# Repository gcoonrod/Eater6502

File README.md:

<!--
 Copyright 2023 Greg Coonrod
 
 Licensed under the Apache License, Version 2.0 (the "License");
 you may not use this file except in compliance with the License.
 You may obtain a copy of the License at
 
     http://www.apache.org/licenses/LICENSE-2.0
 
 Unless required by applicable law or agreed to in writing, software
 distributed under the License is distributed on an "AS IS" BASIS,
 WITHOUT WARRANTIES OR CONDITIONS OF ANY KIND, either express or implied.
 See the License for the specific language governing permissions and
 limitations under the License.
-->

# Eater 6502 - Computer Build

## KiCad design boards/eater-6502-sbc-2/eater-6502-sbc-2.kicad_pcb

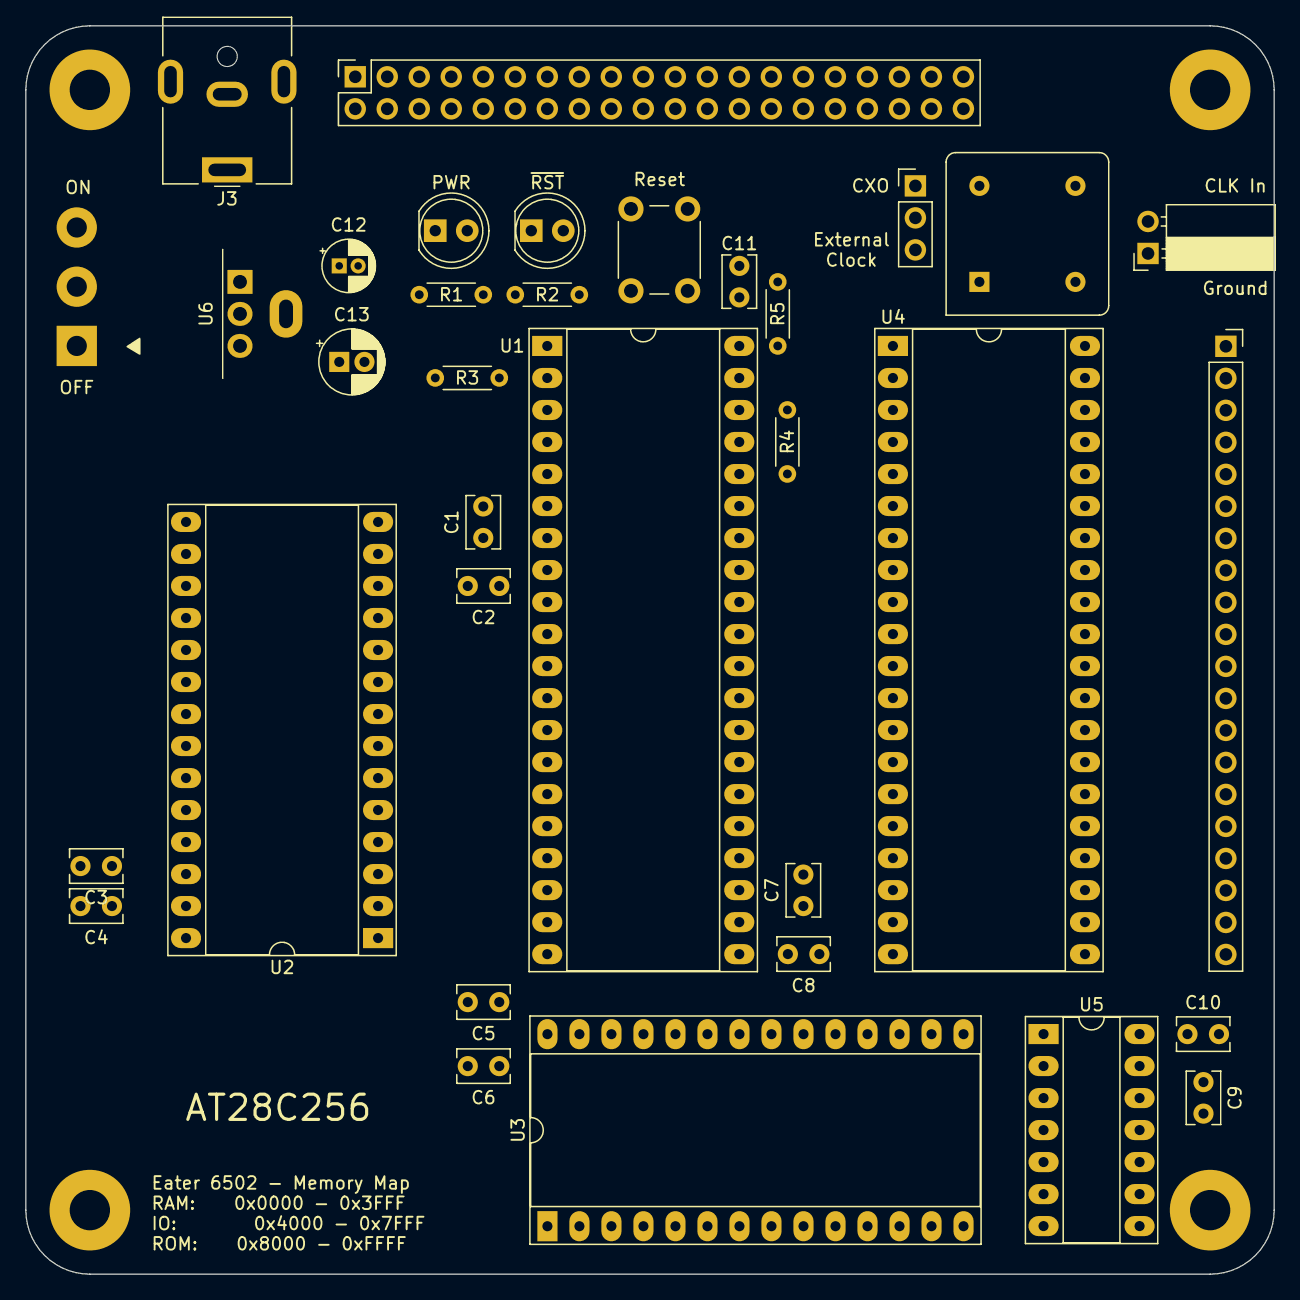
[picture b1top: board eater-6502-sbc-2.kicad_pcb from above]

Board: 2 copper layers, 99.1 x 99.1 mm, 39 parts (0 on the bottom side), 70 nets, no tracks yet.

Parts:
C1, C3, C5, C7, C9: 1u; C_Rect_L4.0mm_W2.5mm_P2.50mm
C2, C4, C6, C8, C10, C11: 100n; C_Rect_L4.0mm_W2.5mm_P2.50mm
C12: 0u33; CP_Radial_D4.0mm_P1.50mm
C13: 10u; CP_Radial_D5.0mm_P2.00mm
D1: LED_PWR; LED_D5.0mm
D2: LED_RST; LED_D5.0mm
H1, H2, H3, H4: M3; MountingHole_3.2mm_M3_Pad
HS1: Heatsink; Heatsink_AAVID_576802B03900G
J1: HDR_EXT_CLK; PinSocket_1x02_P2.54mm_Horizontal
J2: HDR_CPU_BUS; PinSocket_2x20_P2.54mm_Vertical
J3: Jack-DC; BarrelJack_CUI_PJ-063AH_Horizontal
J4: HDR_PIO_PORT; PinSocket_1x20_P2.54mm_Vertical
JP1: JMP_CLK; PinHeader_1x03_P2.54mm_Vertical
R1, R2: 470; R_Axial_DIN0204_L3.6mm_D1.6mm_P5.08mm_Horizontal
R3, R4, R5: 1k; R_Axial_DIN0204_L3.6mm_D1.6mm_P5.08mm_Horizontal
SW1: SW_RESET; SW_PUSH_6mm
SW2: SW_PWR; Button_Switch_SPST_NKK_CS12ANW03
U1: W65C02SxP; DIP-40_W15.24mm_Socket_LongPads
U2: 28C256; DIP-28_W15.24mm_Socket_LongPads
U3: KM62256CLP; DIP-28_W15.24mm_Socket_LongPads
U4: W65C22NxP; DIP-40_W15.24mm_Socket_LongPads
U5: 74HC132; DIP-14_W7.62mm_Socket_LongPads
U6: MC7805; TO-220-3_Vertical
X1: 14 MHz; Oscillator_DIP-8

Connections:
/A0: J2.17, U1.9 (A0), U2.10 (A0), U3.10 (A0), U4.38 (RS0)
/A1: J2.19, U1.10 (A1), U2.9 (A1), U3.9 (A1), U4.37 (RS1)
/A2: J2.21, U1.11 (A2), U2.8 (A2), U3.8 (A2), U4.36 (RS2)
/A3: J2.23, U1.12 (A3), U2.7 (A3), U3.7 (A3), U4.35 (RS3)
/A4: J2.25, U1.13 (A4), U2.6 (A4), U3.6 (A4)
/A5: J2.27, U1.14 (A5), U2.5 (A5), U3.5 (A5)
/A6: J2.29, U1.15 (A6), U2.4 (A6), U3.4 (A6)
/A7: J2.31, U1.16 (A7), U2.3 (A7), U3.3 (A7)
/A8: J2.33, U1.17 (A8), U2.25 (A8), U3.25 (A8)
/A9: J2.35, U1.18 (A9), U2.24 (A9), U3.24 (A9)
/A10: J2.37, U1.19 (A10), U2.21 (A10), U3.21 (A10)
/A11: J2.39, U1.20 (A11), U2.23 (A11), U3.23 (A11)
/A12: J2.38, U1.22 (A12), U2.2 (A12), U3.2 (A12)
/A13: J2.36, U1.23 (A13), U2.26 (A13), U3.26 (A13), U4.24 (CS1)
/A14: J2.34, U1.24 (A14), U2.1 (A14), U3.1 (A14), U3.22 (~OE), U5.5
/A15: J2.32, U1.25 (A15), U5.1, U5.2
/ADDR_~HI: U2.20 (~CS), U5.3, U5.4, U5.9
/BE: J2.10, R4.1, U1.36 (BE)
/CA1: J4.9, U4.40 (CA1)
/CA2: J4.10, U4.39 (CA2)
/CB1: J4.11, U4.18 (CB1)
/CB2: J4.12, U4.19 (CB2)
/CLK: J2.8, JP1.2 (C), U1.37 (ϕ0), U4.25 (ϕ2), U5.10
/CLK2: J2.4, U1.39 (ϕ2)
/CXO: JP1.1 (A), X1.5 (OUT)
/D0: J2.16, U1.33 (D0), U2.11 (D0), U3.11 (Q0), U4.33 (D0)
/D1: J2.18, U1.32 (D1), U2.12 (D1), U3.12 (Q1), U4.32 (D1)
/D2: J2.20, U1.31 (D2), U2.13 (D2), U3.13 (Q2), U4.31 (D2)
/D3: J2.22, U1.30 (D3), U2.15 (D3), U3.15 (Q3), U4.30 (D3)
/D4: J2.24, U1.29 (D4), U2.16 (D4), U3.16 (Q4), U4.29 (D4)
/D5: J2.26, U1.28 (D5), U2.17 (D5), U3.17 (Q5), U4.28 (D5)
/D6: J2.28, U1.27 (D6), U2.18 (D6), U3.18 (Q6), U4.27 (D6)
/D7: J2.30, U1.26 (D7), U2.19 (D7), U3.19 (Q7), U4.26 (D7)
/EXT_CLK: J1.2, JP1.3 (B)
/PA0: J4.1, U4.2 (PA0)
/PA1: J4.2, U4.3 (PA1)
/PA2: J4.3, U4.4 (PA2)
/PA3: J4.4, U4.5 (PA3)
/PA4: J4.5, U4.6 (PA4)
/PA5: J4.6, U4.7 (PA5)
/PA6: J4.7, U4.8 (PA6)
/PA7: J4.8, U4.9 (PA7)
/PB0: J4.13, U4.10 (PB0)
/PB1: J4.14, U4.11 (PB1)
/PB2: J4.15, U4.12 (PB2)
/PB3: J4.16, U4.13 (PB3)
/PB4: J4.17, U4.14 (PB4)
/PB5: J4.18, U4.15 (PB5)
/PB6: J4.19, U4.16 (PB6)
/PB7: J4.20, U4.17 (PB7)
/RAM_~EN: U3.20 (~CS), U5.8
/RDY: J2.3, R3.2, U1.2 (RDY)
/R/~W: J2.14, U1.34 (R/~W), U3.27 (~WE), U4.22 (R/~W)
/SYNC: J2.13, U1.7 (SYNC)
/VIA_~CS2: U4.23 (~CS2), U5.6
/~CLK: J2.5, U1.3 (ϕ1)
/~IRQ: J2.7, U1.4 (~IRQ), U4.21 (~IRQ)
/~ML: J2.9, U1.5 (~ML)
/~NMI: J2.11, U1.6 (~NMI)
/~RES: J2.2, U1.40 (~RES), U4.34 (~RES), U5.12, U5.13
/~RST: C11.2, R5.2, SW1.2
/~SO: J2.6, U1.38 (~SO)
/~VP: J2.1, U1.1 (~VP)
GND: C1.2, C2.2, C3.2, C4.2, C5.2, C6.2, C7.2, C8.2, C9.2, C10.2, C11.1, C12.2, C13.2, H1.1, H2.1, H3.1, H4.1, J1.1, J2.40, J3.2, R1.2, R2.2, SW1.1, U1.21 (VSS), U2.14 (GND), U2.22 (~OE), U3.14 (GND), U4.1 (VSS), U5.7 (GND), U6.2 (GND), X1.4 (GND)
unnamed: D1.1 (K), R1.1
unnamed: D2.1 (K), R2.1
unnamed: D2.2 (A), U5.11
unnamed: J3.1, SW2.2 (B)
VCC: C1.1, C2.1, C3.1, C4.1, C5.1, C6.1, C7.1, C8.1, C9.1, C10.1, C13.1, D1.2 (A), J2.15, R3.1, R4.2, R5.1, U1.8 (VDD), U2.27 (~WE), U2.28 (VCC), U3.28 (VCC), U4.20 (VCC), U5.14 (VCC), U6.3 (VO), X1.8 (Vcc)
VDC: C12.1, SW2.3 (C), U6.1 (VI)

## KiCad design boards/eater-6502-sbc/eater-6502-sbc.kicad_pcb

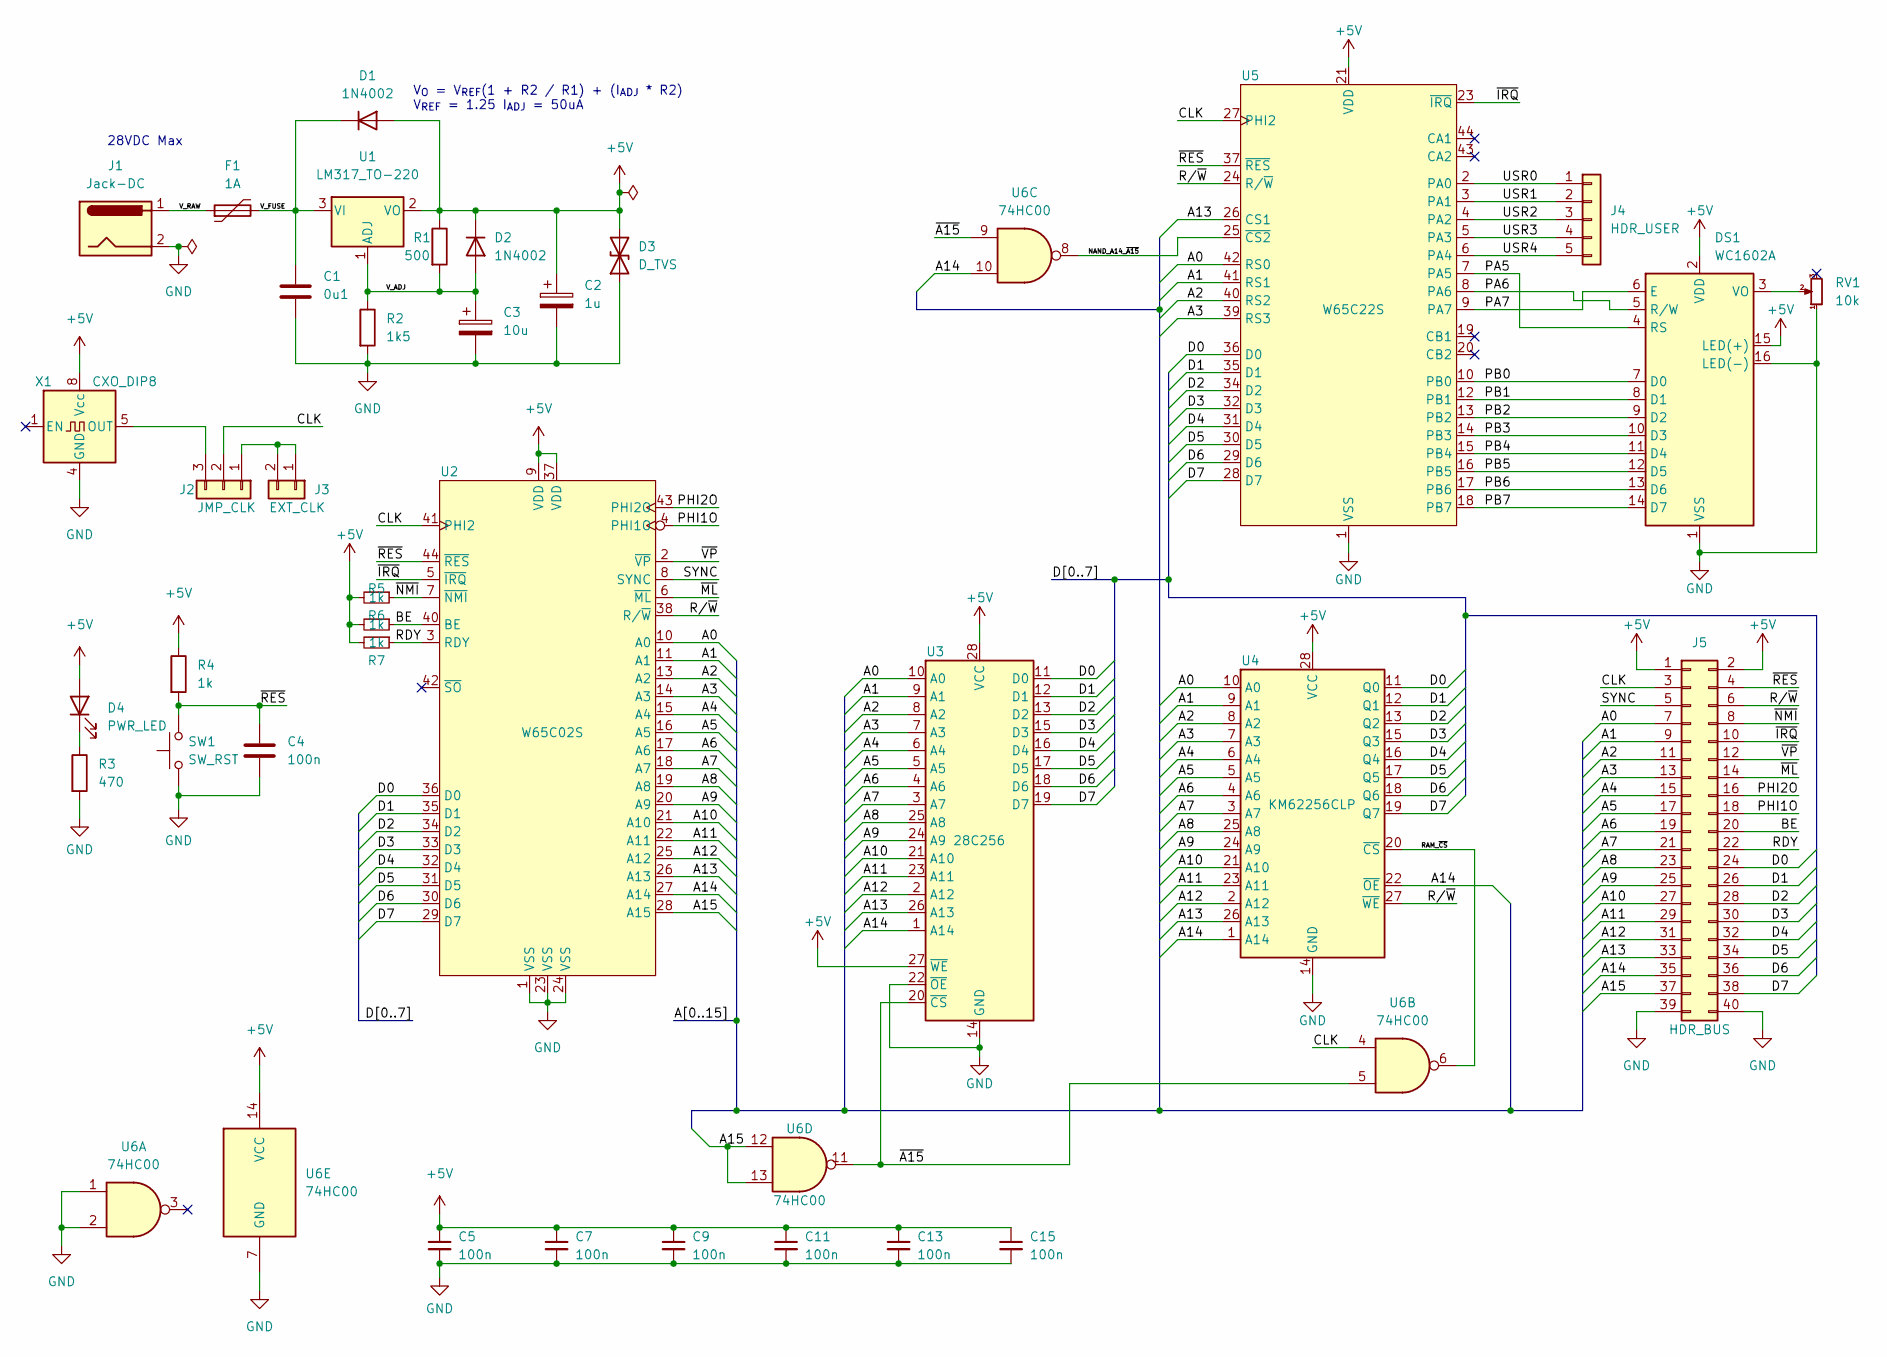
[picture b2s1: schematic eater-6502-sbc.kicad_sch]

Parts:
C1: 0u1; C_Disc_D3.4mm_W2.1mm_P2.50mm
C2: 1u; CP_Radial_D4.0mm_P1.50mm
C3: 10u; CP_Radial_D5.0mm_P2.00mm
C4, C5, C7, C9, C11, C13, C15: 100n; C_Disc_D3.4mm_W2.1mm_P2.50mm
D1, D2: 1N4002; D_DO-41_SOD81_P10.16mm_Horizontal
D3: D_TVS; D_DO-41_SOD81_P7.62mm_Horizontal
D4: PWR_LED; LED_D5.0mm
DS1: WC1602A
F1: 1A; Fuse_BelFuse_0ZRE0005FF_L8.3mm_W3.8mm
J1: Jack-DC; BarrelJack_CUI_PJ-063AH_Horizontal
J2: JMP_CLK; PinHeader_1x03_P2.54mm_Vertical
J3: EXT_CLK; PinSocket_1x02_P2.54mm_Vertical
J4: HDR_USER; PinSocket_1x05_P2.54mm_Vertical
J5: HDR_BUS; PinSocket_2x20_P2.54mm_Vertical
R1: 500; R_Axial_DIN0207_L6.3mm_D2.5mm_P10.16mm_Horizontal
R2: 1k5; R_Axial_DIN0207_L6.3mm_D2.5mm_P10.16mm_Horizontal
R3: 470; R_Axial_DIN0204_L3.6mm_D1.6mm_P5.08mm_Horizontal
R4, R5, R6, R7: 1k; R_Axial_DIN0204_L3.6mm_D1.6mm_P5.08mm_Horizontal
RV1: 10k; Potentiometer_Bourns_3266W_Vertical
SW1: SW_RST; SW_PUSH_6mm
U1: LM317_TO-220; TO-220-3_Vertical; Manufacturer Part Number LM317KCS
U2: W65C02S; PLCC-44_THT-Socket; Manufacturer Part Number W65C02S6TPLG-14
U3: 28C256; DIP_Socket-28_W11.9_W12.7_W15.24_W17.78_W18.5_3M_228-1277-0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; Manufacturer Part Number 28-6554-10
U4: KM62256CLP; DIP-28_W15.24mm_Socket_LongPads; Manufacturer Part Number AS6C62256-55PCN
U5: W65C22S; PLCC-44_THT-Socket; Manufacturer Part Number W65C22S6TPLG-14
U6: 74HC00; DIP-14_W7.62mm_LongPads
X1: CXO_DIP8; Oscillator_DIP-8_LargePads

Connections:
+5V: C2.1, C5.1, C7.1, C9.1, C11.1, C13.1, C15.1, D1.2 (A), D2.1 (K), D3.2 (A2), D4.2 (A), DS1.2 (VDD), DS1.15 (LED(+)), J5.1, J5.2, R1.1, R4.1, R5.2, R6.2, R7.2, U1.2 (VO), U2.9 (VDD), U2.37 (VDD), U3.27 (~WE), U3.28 (VCC), U4.28 (VCC), U5.21 (VDD), U6.14 (VCC), X1.8 (Vcc)
/A0: J5.7, U2.10 (A0), U3.10 (A0), U4.10 (A0), U5.42 (RS0)
/A1: J5.9, U2.11 (A1), U3.9 (A1), U4.9 (A1), U5.41 (RS1)
/A2: J5.11, U2.13 (A2), U3.8 (A2), U4.8 (A2), U5.40 (RS2)
/A3: J5.13, U2.14 (A3), U3.7 (A3), U4.7 (A3), U5.39 (RS3)
/A4: J5.15, U2.15 (A4), U3.6 (A4), U4.6 (A4)
/A5: J5.17, U2.16 (A5), U3.5 (A5), U4.5 (A5)
/A6: J5.19, U2.17 (A6), U3.4 (A6), U4.4 (A6)
/A7: J5.21, U2.18 (A7), U3.3 (A7), U4.3 (A7)
/A8: J5.23, U2.19 (A8), U3.25 (A8), U4.25 (A8)
/A9: J5.25, U2.20 (A9), U3.24 (A9), U4.24 (A9)
/A10: J5.27, U2.21 (A10), U3.21 (A10), U4.21 (A10)
/A11: J5.29, U2.22 (A11), U3.23 (A11), U4.23 (A11)
/A12: J5.31, U2.25 (A12), U3.2 (A12), U4.2 (A12)
/A13: J5.33, U2.26 (A13), U3.26 (A13), U4.26 (A13), U5.26 (CS1)
/A14: J5.35, U2.27 (A14), U3.1 (A14), U4.1 (A14), U4.22 (~OE), U6.10
/A15: J5.37, U2.28 (A15), U6.12, U6.13
/BE: J5.20, R6.1, U2.40 (BE)
/CLK: J2.2, J5.3, U2.41 (PHI2), U5.27 (PHI2), U6.4
/D0: J5.24, U2.36 (D0), U3.11 (D0), U4.11 (Q0), U5.36 (D0)
/D1: J5.26, U2.35 (D1), U3.12 (D1), U4.12 (Q1), U5.35 (D1)
/D2: J5.28, U2.34 (D2), U3.13 (D2), U4.13 (Q2), U5.34 (D2)
/D3: J5.30, U2.33 (D3), U3.15 (D3), U4.15 (Q3), U5.32 (D3)
/D4: J5.32, U2.32 (D4), U3.16 (D4), U4.16 (Q4), U5.31 (D4)
/D5: J5.34, U2.31 (D5), U3.17 (D5), U4.17 (Q5), U5.30 (D5)
/D6: J5.36, U2.30 (D6), U3.18 (D6), U4.18 (Q6), U5.29 (D6)
/D7: J5.38, U2.29 (D7), U3.19 (D7), U4.19 (Q7), U5.28 (D7)
/NAND_A14_~A15: U5.25 (~CS2), U6.8
/PA5: DS1.4 (RS), U5.7 (PA5)
/PA6: DS1.5 (R/W), U5.8 (PA6)
/PA7: DS1.6 (E), U5.9 (PA7)
/PB0: DS1.7 (D0), U5.10 (PB0)
/PB1: DS1.8 (D1), U5.12 (PB1)
/PB2: DS1.9 (D2), U5.13 (PB2)
/PB3: DS1.10 (D3), U5.14 (PB3)
/PB4: DS1.11 (D4), U5.15 (PB4)
/PB5: DS1.12 (D5), U5.16 (PB5)
/PB6: DS1.13 (D6), U5.17 (PB6)
/PB7: DS1.14 (D7), U5.18 (PB7)
/PHI1O: J5.18, U2.4 (PHI1O)
/PHI2O: J5.16, U2.43 (PHI2O)
/RAM_~CS: U4.20 (~CS), U6.6
/RDY: J5.22, R7.1, U2.3 (RDY)
/R/~W: J5.6, U2.38 (R/~W), U4.27 (~WE), U5.24 (R/~W)
/SYNC: J5.5, U2.8 (SYNC)
/USR0: J4.1, U5.2 (PA0)
/USR1: J4.2, U5.3 (PA1)
/USR2: J4.3, U5.4 (PA2)
/USR3: J4.4, U5.5 (PA3)
/USR4: J4.5, U5.6 (PA4)
/V_ADJ: C3.1, D2.2 (A), R1.2, R2.1, U1.1 (ADJ)
/V_FUSE: C1.1, D1.1 (K), F1.2, U1.3 (VI)
/V_RAW: F1.1, J1.1
/~A15: U3.20 (~CS), U6.5, U6.9, U6.11
/~IRQ: J5.10, U2.5 (~IRQ), U5.23 (~IRQ)
/~ML: J5.14, U2.6 (~ML)
/~NMI: J5.8, R5.1, U2.7 (~NMI)
/~RES: C4.1, J5.4, R4.2, SW1.2, U2.44 (~RES), U5.37 (~RES)
/~VP: J5.12, U2.2 (~VP)
GND: C1.2, C2.2, C3.2, C4.2, C5.2, C7.2, C9.2, C11.2, C13.2, C15.2, D3.1 (A1), DS1.1 (VSS), DS1.16 (LED(-)), J1.2, J5.39, J5.40, R2.2, R3.2, RV1.1, SW1.1, U2.1 (VSS), U2.23 (VSS), U2.24 (VSS), U3.14 (GND), U3.22 (~OE), U4.14 (GND), U5.1 (VSS), U6.1, U6.2, U6.7 (GND), X1.4 (GND)
unnamed: D4.1 (K), R3.1
unnamed: DS1.3 (VO), RV1.2
unnamed: J2.1, J3.1, J3.2
unnamed: J2.3, X1.5 (OUT)

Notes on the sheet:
V_{O} = V_{REF}(1 + R2 / R1) + (I_{ADJ} * R2) V_{REF} = 1.25 I_{ADJ} = 50uA
28VDC Max

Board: 2 copper layers, 37 parts (0 on the bottom side), 64 nets, no tracks yet.

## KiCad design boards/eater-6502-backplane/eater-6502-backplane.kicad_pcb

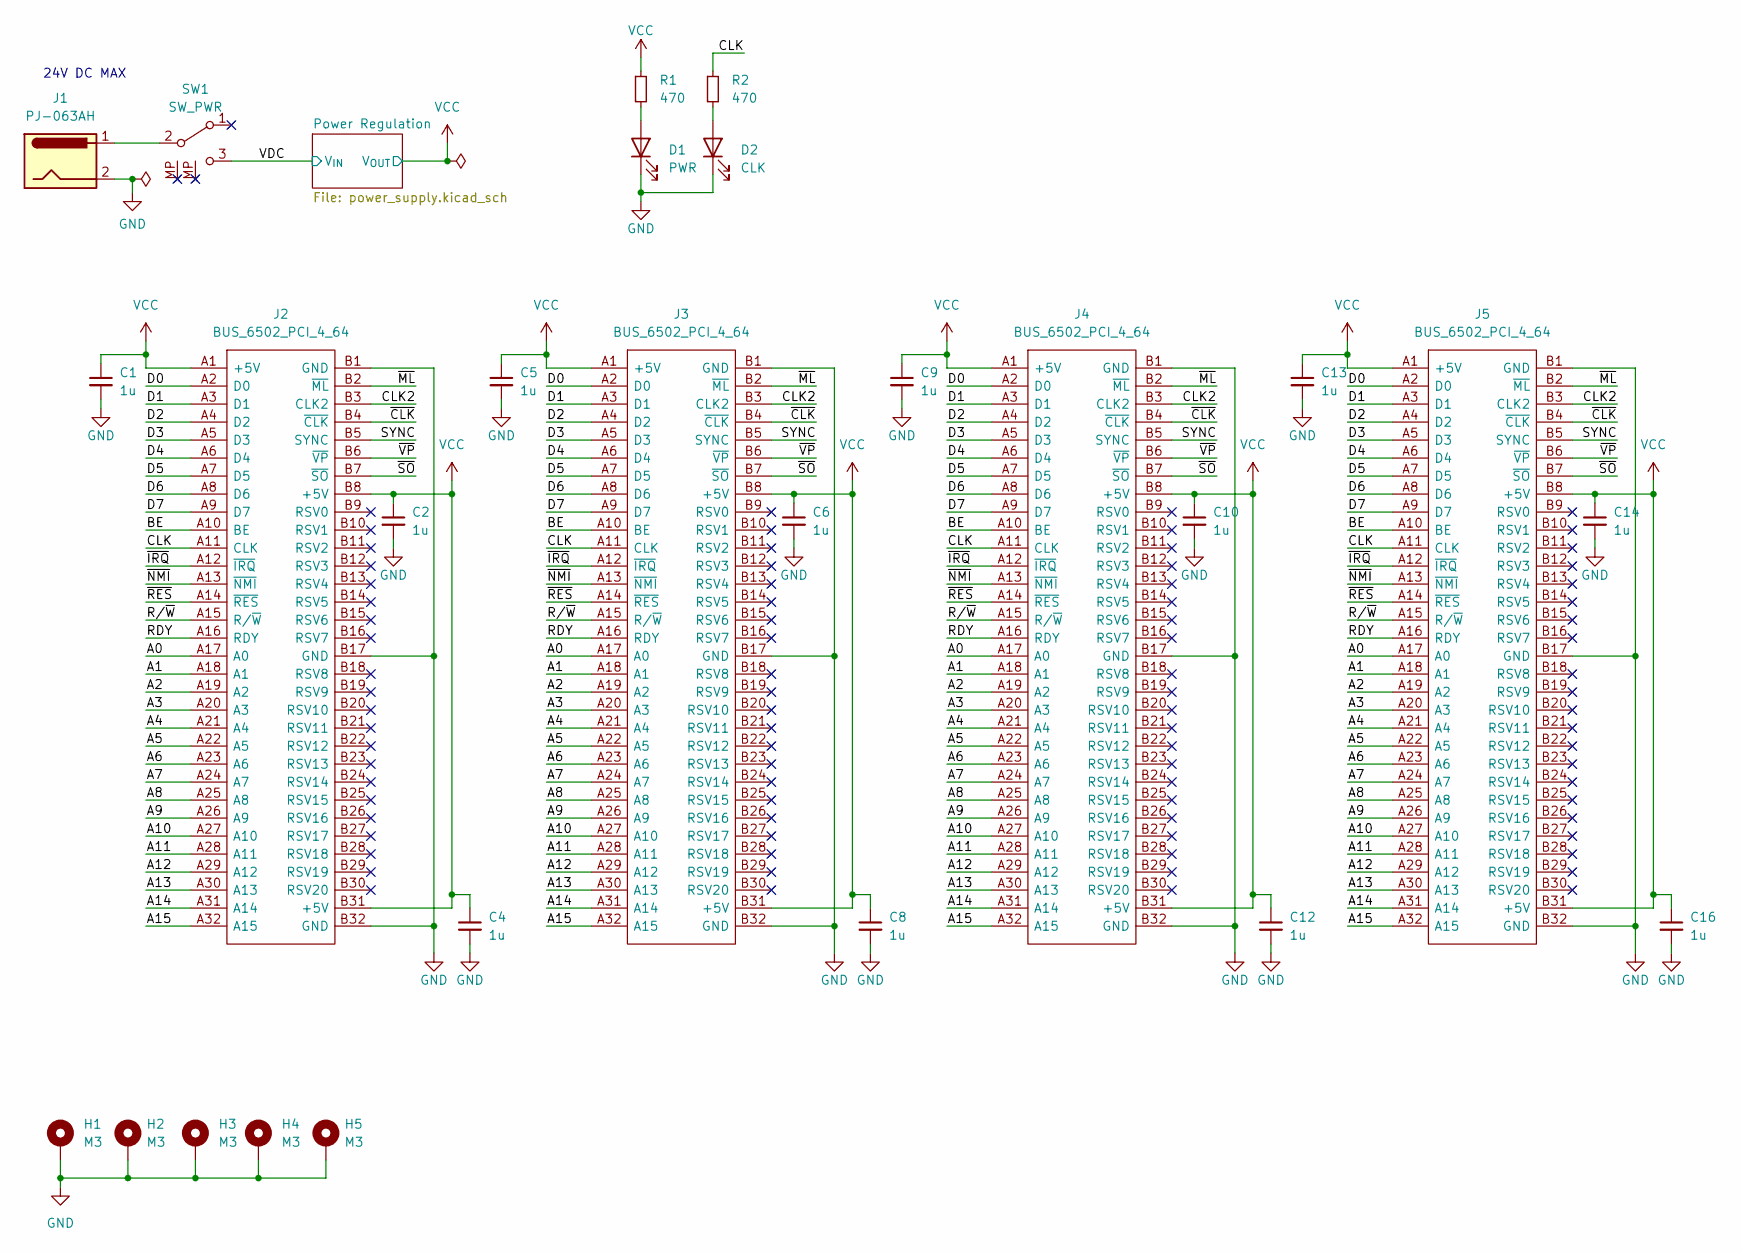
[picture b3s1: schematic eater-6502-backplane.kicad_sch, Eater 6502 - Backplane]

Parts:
C1, C2, C4, C5, C6, C8, C9, C10, C12, C13, C14, C16: 1u; C_Rect_L4.0mm_W2.5mm_P2.50mm; Manufacturer Part Number FG18X5R1H105KRT06
D1: PWR; LED_D5.0mm
D2: CLK; LED_D5.0mm
H1, H2, H3, H4, H5: M3; MountingHole_3.2mm_M3_Pad_Via
J1: PJ-063AH; BarrelJack_CUI_PJ-063AH_Horizontal; Manufacturer Part Number PJ-063AH
J2, J3, J4, J5: BUS_6502_PCI_4_64; 877159100 PCIe x4; Mouser Part Number 538-87715-9100
R1, R2: 470; R_Axial_DIN0207_L6.3mm_D2.5mm_P7.62mm_Horizontal; Manufacturer Part Number RNF14FTD470R
SW1: SW_PWR; Button_Switch_Dailywell_SPDT; Manufacturer Part Number 5MS1S102AM6QES

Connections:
/A0: J2.A17 (A0), J3.A17 (A0), J4.A17 (A0), J5.A17 (A0)
/A1: J2.A18 (A1), J3.A18 (A1), J4.A18 (A1), J5.A18 (A1)
/A2: J2.A19 (A2), J3.A19 (A2), J4.A19 (A2), J5.A19 (A2)
/A3: J2.A20 (A3), J3.A20 (A3), J4.A20 (A3), J5.A20 (A3)
/A4: J2.A21 (A4), J3.A21 (A4), J4.A21 (A4), J5.A21 (A4)
/A5: J2.A22 (A5), J3.A22 (A5), J4.A22 (A5), J5.A22 (A5)
/A6: J2.A23 (A6), J3.A23 (A6), J4.A23 (A6), J5.A23 (A6)
/A7: J2.A24 (A7), J3.A24 (A7), J4.A24 (A7), J5.A24 (A7)
/A8: J2.A25 (A8), J3.A25 (A8), J4.A25 (A8), J5.A25 (A8)
/A9: J2.A26 (A9), J3.A26 (A9), J4.A26 (A9), J5.A26 (A9)
/A10: J2.A27 (A10), J3.A27 (A10), J4.A27 (A10), J5.A27 (A10)
/A11: J2.A28 (A11), J3.A28 (A11), J4.A28 (A11), J5.A28 (A11)
/A12: J2.A29 (A12), J3.A29 (A12), J4.A29 (A12), J5.A29 (A12)
/A13: J2.A30 (A13), J3.A30 (A13), J4.A30 (A13), J5.A30 (A13)
/A14: J2.A31 (A14), J3.A31 (A14), J4.A31 (A14), J5.A31 (A14)
/A15: J2.A32 (A15), J3.A32 (A15), J4.A32 (A15), J5.A32 (A15)
/BE: J2.A10 (BE), J3.A10 (BE), J4.A10 (BE), J5.A10 (BE)
/CLK: J2.A11 (CLK), J3.A11 (CLK), J4.A11 (CLK), J5.A11 (CLK), R2.1
/CLK2: J2.B3 (CLK2), J3.B3 (CLK2), J4.B3 (CLK2), J5.B3 (CLK2)
/D0: J2.A2 (D0), J3.A2 (D0), J4.A2 (D0), J5.A2 (D0)
/D1: J2.A3 (D1), J3.A3 (D1), J4.A3 (D1), J5.A3 (D1)
/D2: J2.A4 (D2), J3.A4 (D2), J4.A4 (D2), J5.A4 (D2)
/D3: J2.A5 (D3), J3.A5 (D3), J4.A5 (D3), J5.A5 (D3)
/D4: J2.A6 (D4), J3.A6 (D4), J4.A6 (D4), J5.A6 (D4)
/D5: J2.A7 (D5), J3.A7 (D5), J4.A7 (D5), J5.A7 (D5)
/D6: J2.A8 (D6), J3.A8 (D6), J4.A8 (D6), J5.A8 (D6)
/D7: J2.A9 (D7), J3.A9 (D7), J4.A9 (D7), J5.A9 (D7)
/RDY: J2.A16 (RDY), J3.A16 (RDY), J4.A16 (RDY), J5.A16 (RDY)
/R/~W: J2.A15 (R/~W), J3.A15 (R/~W), J4.A15 (R/~W), J5.A15 (R/~W)
/SYNC: J2.B5 (SYNC), J3.B5 (SYNC), J4.B5 (SYNC), J5.B5 (SYNC)
/VDC: SW1.3 (C); also elsewhere on the board
/~CLK: J2.B4 (~CLK), J3.B4 (~CLK), J4.B4 (~CLK), J5.B4 (~CLK)
/~IRQ: J2.A12 (~IRQ), J3.A12 (~IRQ), J4.A12 (~IRQ), J5.A12 (~IRQ)
/~ML: J2.B2 (~ML), J3.B2 (~ML), J4.B2 (~ML), J5.B2 (~ML)
/~NMI: J2.A13 (~NMI), J3.A13 (~NMI), J4.A13 (~NMI), J5.A13 (~NMI)
/~RES: J2.A14 (~RES), J3.A14 (~RES), J4.A14 (~RES), J5.A14 (~RES)
/~SO: J2.B7 (~SO), J3.B7 (~SO), J4.B7 (~SO), J5.B7 (~SO)
/~VP: J2.B6 (~VP), J3.B6 (~VP), J4.B6 (~VP), J5.B6 (~VP)
GND: C1.2, C2.2, C4.2, C5.2, C6.2, C8.2, C9.2, C10.2, C12.2, C13.2, C14.2, C16.2, D1.1 (K), D2.1 (K), H1.1, H2.1, H3.1, H4.1, H5.1, J1.2, J2.B1 (GND), J2.B17 (GND), J2.B32 (GND), J3.B1 (GND), J3.B17 (GND), J3.B32 (GND), J4.B1 (GND), J4.B17 (GND), J4.B32 (GND), J5.B1 (GND), J5.B17 (GND), J5.B32 (GND); also elsewhere on the board
unnamed: D1.2 (A), R1.2
unnamed: D2.2 (A), R2.2
unnamed: J1.1, SW1.2 (B)
VCC: C1.1, C2.1, C4.1, C5.1, C6.1, C8.1, C9.1, C10.1, C12.1, C13.1, C14.1, C16.1, J2.A1 (+5V), J2.B8 (+5V), J2.B31 (+5V), J3.A1 (+5V), J3.B8 (+5V), J3.B31 (+5V), J4.A1 (+5V), J4.B8 (+5V), J4.B31 (+5V), J5.A1 (+5V), J5.B8 (+5V), J5.B31 (+5V), R1.1; also elsewhere on the board

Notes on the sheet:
24V DC MAX

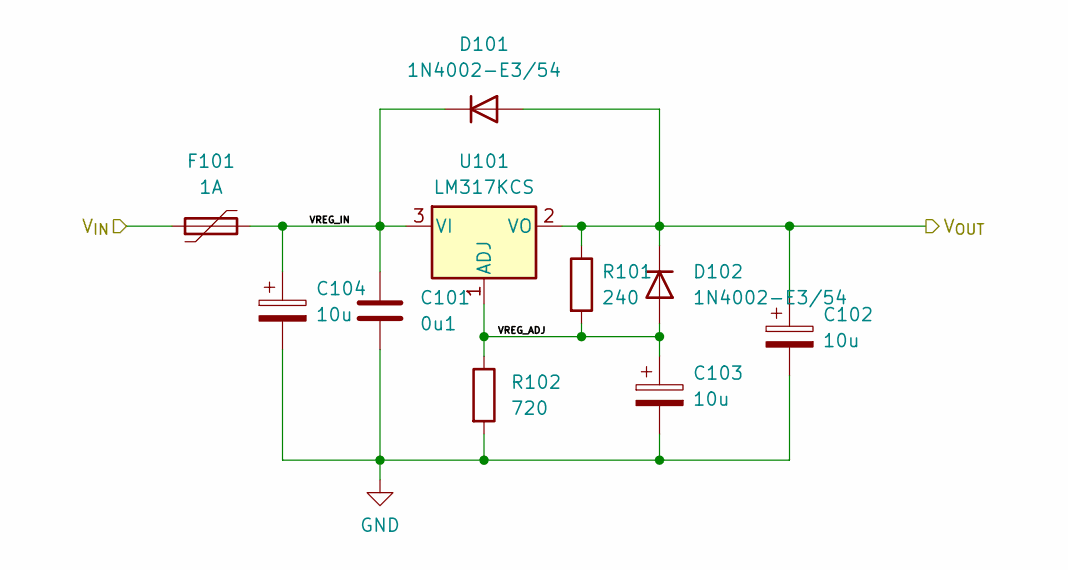
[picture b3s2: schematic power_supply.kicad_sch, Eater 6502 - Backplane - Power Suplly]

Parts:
C101: 0u1; C_Disc_D4.3mm_W1.9mm_P5.00mm; Manufacturer Part Number K104K15X7RF5TH5
C102, C103, C104: 10u; CP_Radial_D5.0mm_P2.00mm; Manufacturer Part Number 860010572002
D101, D102: 1N4002-E3/54; D_DO-41_SOD81_P10.16mm_Horizontal; Manufacturer Part Number 1N4002-E3/54
F101: 1A; Fuse_BelFuse_0ZRE0025FF_L9.6mm_W3.8mm; Manufacturer Part Number 0ZRM0050FF1E
R101: 240; R_Axial_DIN0207_L6.3mm_D2.5mm_P10.16mm_Horizontal; Manufacturer Part Number SFR2500002400FR500
R102: 720; R_Axial_DIN0207_L6.3mm_D2.5mm_P10.16mm_Horizontal; Manufacturer Part Number MFR-25FTF52-720R
U101: LM317KCS; TO-220-3_Vertical; Manufacturer Part Number LM317KCS

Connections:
/Power Regulation/VREG_ADJ: C103.1, D102.2 (A), R101.2, R102.1, U101.1 (ADJ)
/Power Regulation/VREG_IN: C101.1, C104.1, D101.1 (K), F101.2, U101.3 (VI)
/VDC: F101.1; also elsewhere on the board
GND: C101.2, C102.2, C103.2, C104.2, R102.2; also elsewhere on the board
VCC: C102.1, D101.2 (A), D102.1 (K), R101.1, U101.2 (VO); also elsewhere on the board

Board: 2 copper layers, 37 parts (0 on the bottom side), 45 nets, no tracks yet.

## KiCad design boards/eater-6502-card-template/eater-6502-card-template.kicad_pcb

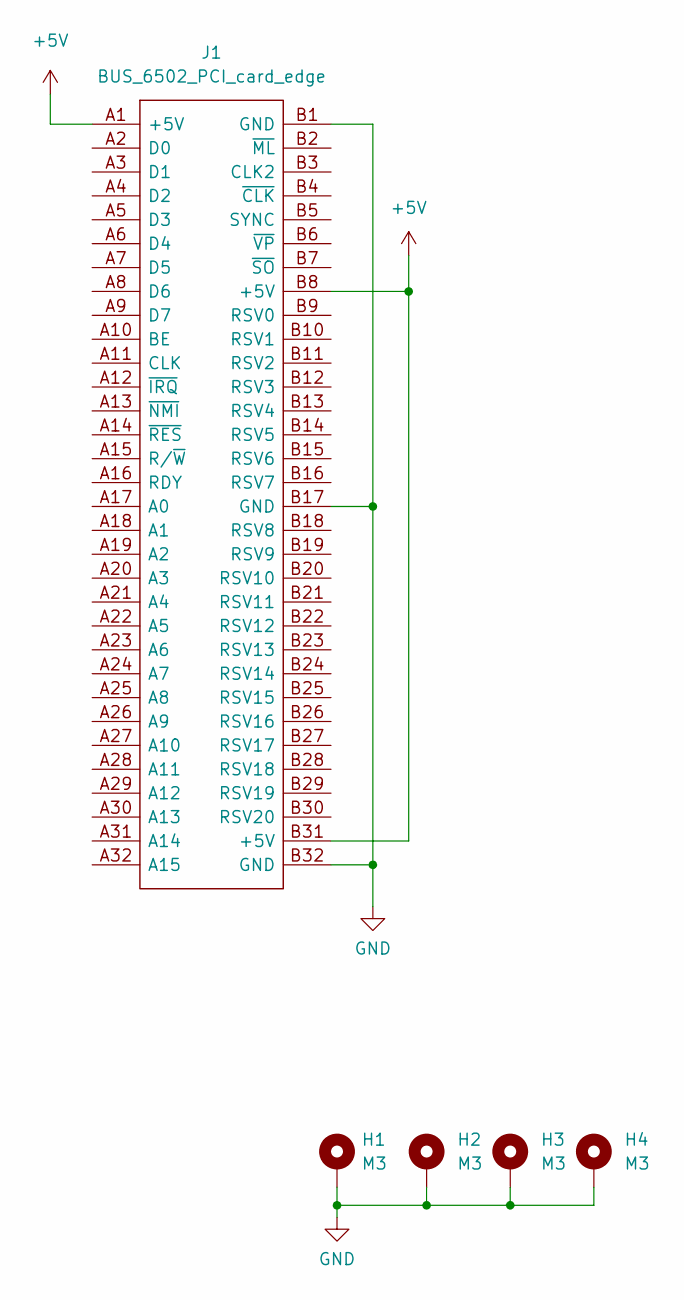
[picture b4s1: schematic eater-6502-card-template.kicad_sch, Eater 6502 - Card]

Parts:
H1, H2, H3, H4: M3; MountingHole_3.2mm_M3_Pad_Via
J1: BUS_6502_PCI_card_edge; BUS_Eater6502_PCI_x4; Mouser Part Number 538-87715-9100

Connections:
+5V: J1.A1 (+5V), J1.B8 (+5V), J1.B31 (+5V)
GND: H1.1, H2.1, H3.1, H4.1, J1.B1 (GND), J1.B17 (GND), J1.B32 (GND)

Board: 2 copper layers, 5 parts (1 on the bottom side), 2 nets, no tracks yet.

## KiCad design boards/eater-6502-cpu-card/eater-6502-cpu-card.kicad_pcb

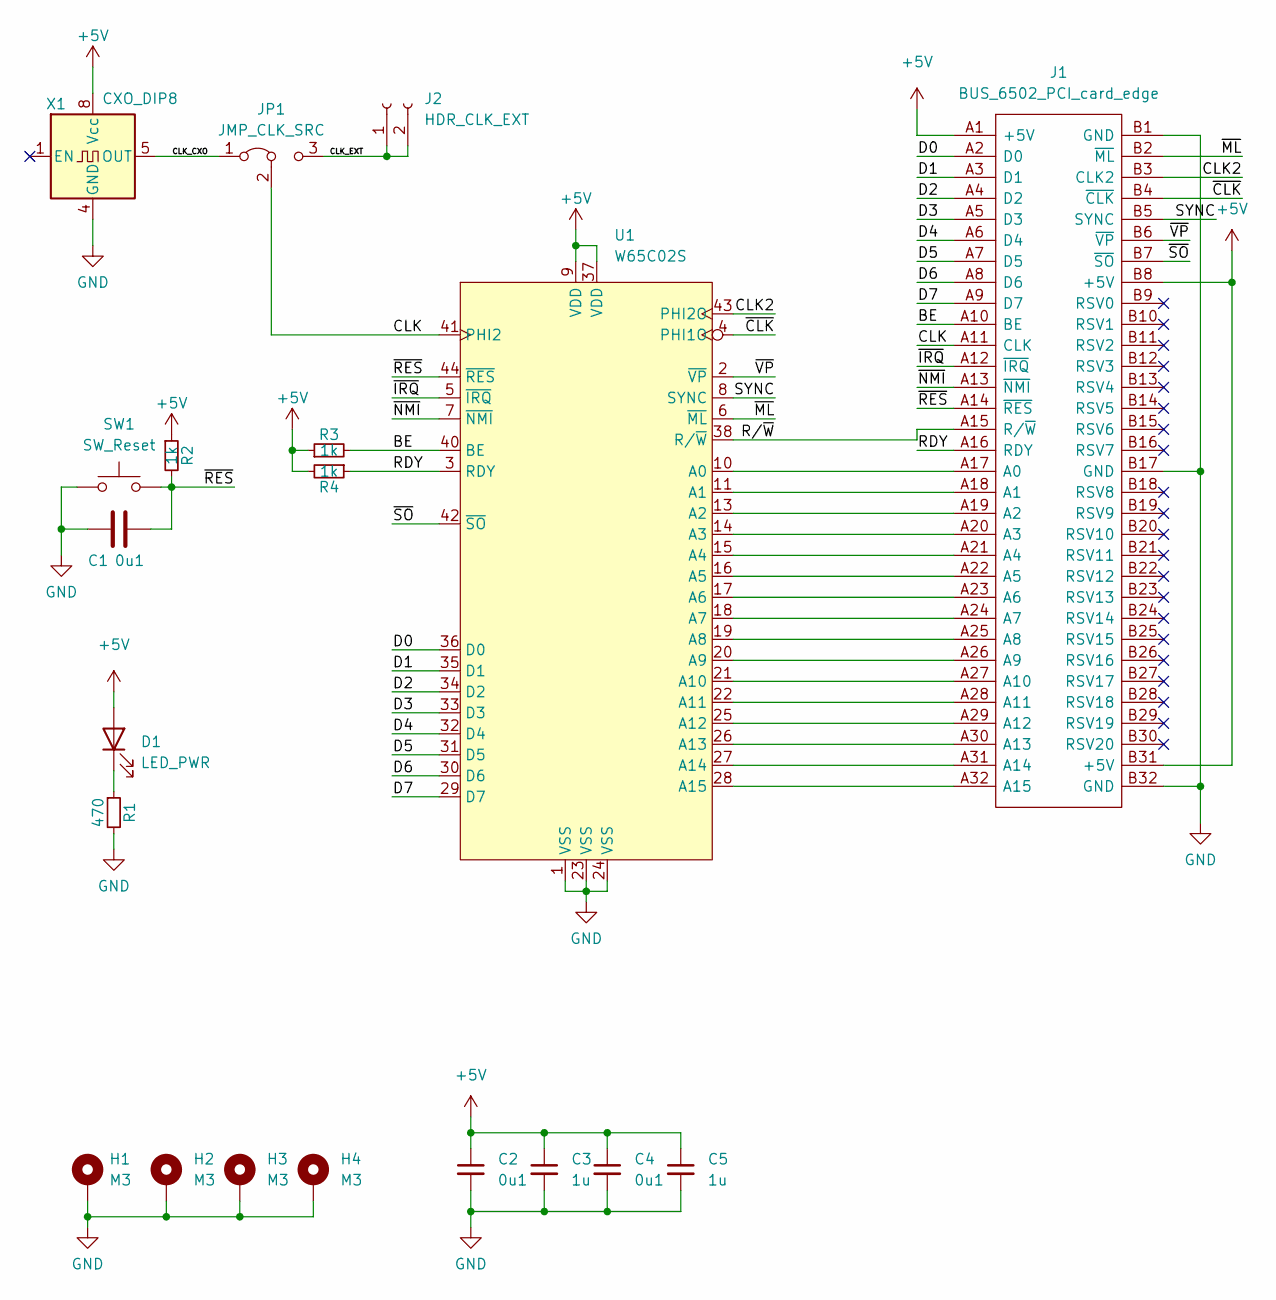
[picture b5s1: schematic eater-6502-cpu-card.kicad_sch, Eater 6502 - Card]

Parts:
C1, C2, C4: 0u1; C_Disc_D3.4mm_W2.1mm_P2.50mm
C3, C5: 1u; C_Disc_D3.4mm_W2.1mm_P2.50mm
D1: LED_PWR; LED_D3.0mm_Horizontal_O1.27mm_Z2.0mm
H1, H2, H3, H4: M3; MountingHole_3.2mm_M3_Pad_Via
J1: BUS_6502_PCI_card_edge; BUS_Eater6502_PCI_x4; Mouser Part Number 538-87715-9100
J2: HDR_CLK_EXT; PinSocket_1x02_P2.54mm_Horizontal
JP1: JMP_CLK_SRC; PinHeader_1x03_P2.54mm_Horizontal
R1: 470; R_Axial_DIN0204_L3.6mm_D1.6mm_P5.08mm_Horizontal
R2, R3, R4: 1k; R_Axial_DIN0204_L3.6mm_D1.6mm_P5.08mm_Horizontal
SW1: SW_Reset; SW_Tactile_SPST_Angled_PTS645Vx39-2LFS
U1: W65C02S; PLCC-44_THT-Socket
X1: CXO_DIP8; Oscillator_DIP-8

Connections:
+5V: C2.1, C3.1, C4.1, C5.1, D1.2 (A), J1.A1 (+5V), J1.B8 (+5V), J1.B31 (+5V), R2.1, R3.1, R4.2, U1.9 (VDD), U1.37 (VDD), X1.8 (Vcc)
/BE: J1.A10 (BE), R3.2, U1.40 (BE)
/CLK: J1.A11 (CLK), JP1.2 (C), U1.41 (PHI2)
/CLK2: J1.B3 (CLK2), U1.43 (PHI2O)
/CLK_CXO: JP1.1 (A), X1.5 (OUT)
/CLK_EXT: J2.1, J2.2, JP1.3 (B)
/D0: J1.A2 (D0), U1.36 (D0)
/D1: J1.A3 (D1), U1.35 (D1)
/D2: J1.A4 (D2), U1.34 (D2)
/D3: J1.A5 (D3), U1.33 (D3)
/D4: J1.A6 (D4), U1.32 (D4)
/D5: J1.A7 (D5), U1.31 (D5)
/D6: J1.A8 (D6), U1.30 (D6)
/D7: J1.A9 (D7), U1.29 (D7)
/RDY: J1.A16 (RDY), R4.1, U1.3 (RDY)
/R/~W: J1.A15 (R/~W), U1.38 (R/~W)
/SYNC: J1.B5 (SYNC), U1.8 (SYNC)
/~CLK: J1.B4 (~CLK), U1.4 (PHI1O)
/~IRQ: J1.A12 (~IRQ), U1.5 (~IRQ)
/~ML: J1.B2 (~ML), U1.6 (~ML)
/~NMI: J1.A13 (~NMI), U1.7 (~NMI)
/~RES: C1.2, J1.A14 (~RES), R2.2, SW1.2, U1.44 (~RES)
/~SO: J1.B7 (~SO), U1.42 (~SO)
/~VP: J1.B6 (~VP), U1.2 (~VP)
GND: C1.1, C2.2, C3.2, C4.2, C5.2, H1.1, H2.1, H3.1, H4.1, J1.B1 (GND), J1.B17 (GND), J1.B32 (GND), R1.2, SW1.1, U1.1 (VSS), U1.23 (VSS), U1.24 (VSS), X1.4 (GND)
unnamed: D1.1 (K), R1.1
unnamed: J1.A17 (A0), U1.10 (A0)
unnamed: J1.A23 (A6), U1.17 (A6)
unnamed: J1.A18 (A1), U1.11 (A1)
unnamed: J1.A19 (A2), U1.13 (A2)
unnamed: J1.A20 (A3), U1.14 (A3)
unnamed: J1.A21 (A4), U1.15 (A4)
unnamed: J1.A22 (A5), U1.16 (A5)
unnamed: J1.A24 (A7), U1.18 (A7)
unnamed: J1.A25 (A8), U1.19 (A8)
unnamed: J1.A26 (A9), U1.20 (A9)
unnamed: J1.A27 (A10), U1.21 (A10)
unnamed: J1.A28 (A11), U1.22 (A11)
unnamed: J1.A29 (A12), U1.25 (A12)
unnamed: J1.A30 (A13), U1.26 (A13)
unnamed: J1.A31 (A14), U1.27 (A14)
unnamed: J1.A32 (A15), U1.28 (A15)

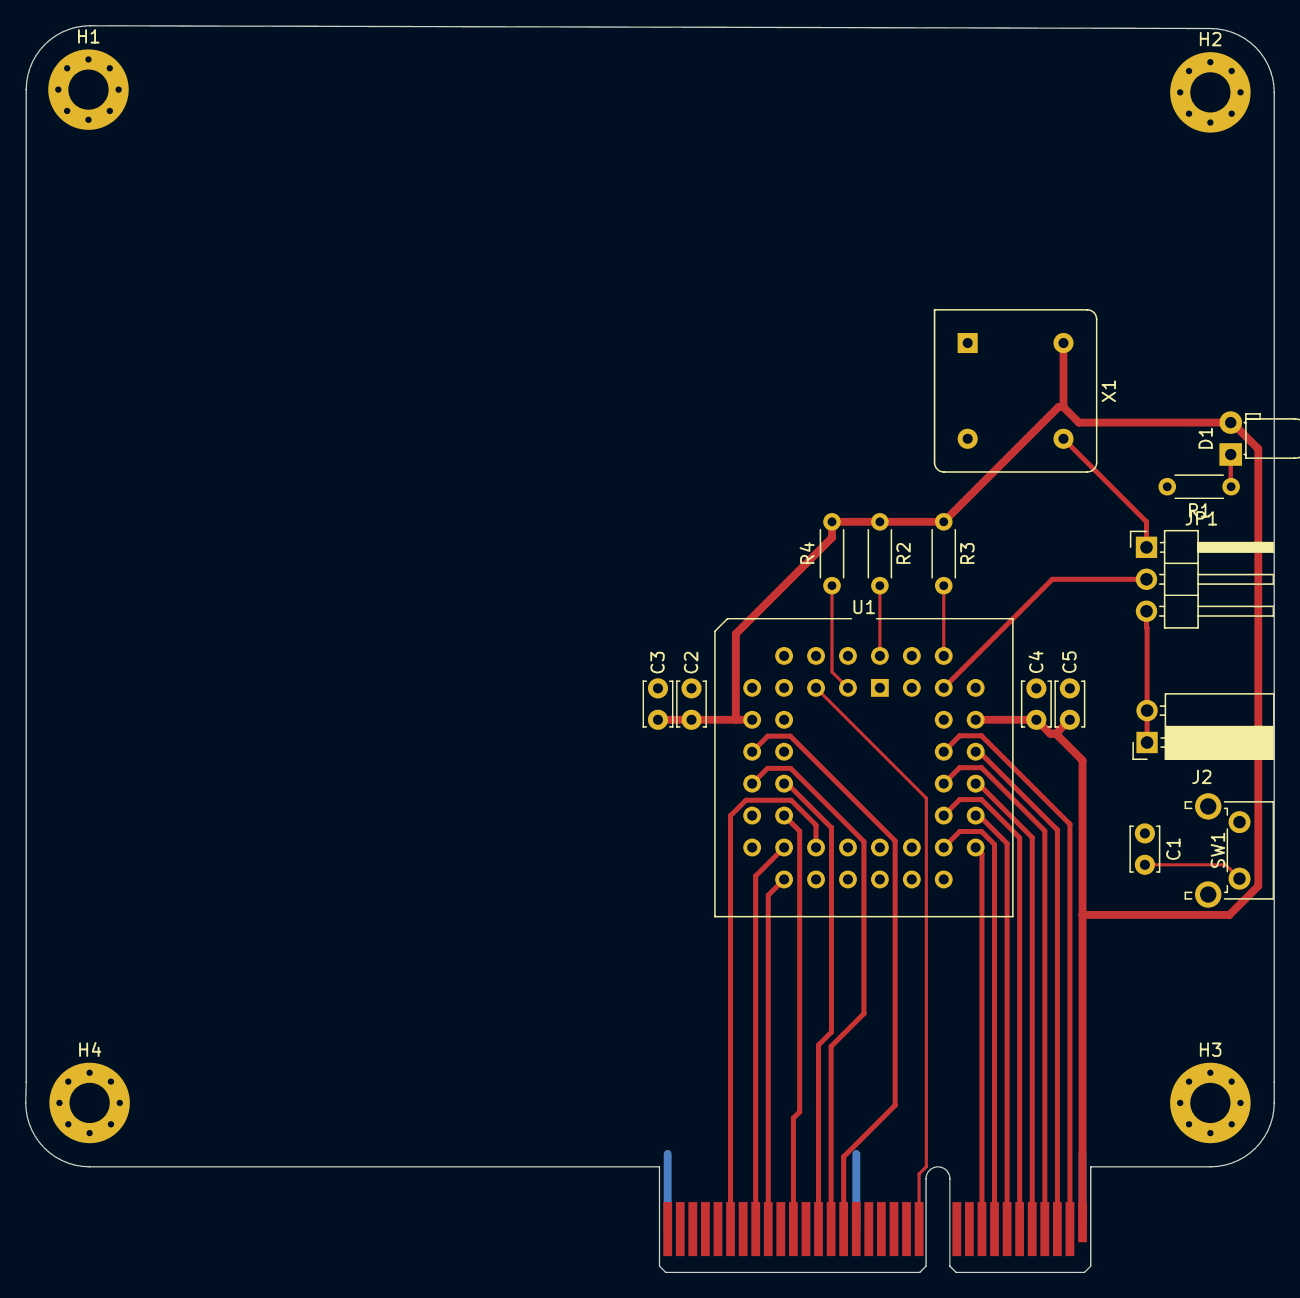
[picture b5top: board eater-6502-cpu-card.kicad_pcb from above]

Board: 2 copper layers, 99.3 x 99.2 mm, 20 parts (1 on the bottom side), 42 nets.

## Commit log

2023-02-25 initial
2023-02-26 Initial blink asm with 65c22
2023-03-02 Started multiple board layouts
2023-03-05 SBC design 2 start
2023-03-06 Finished rough layout and parts selection.
